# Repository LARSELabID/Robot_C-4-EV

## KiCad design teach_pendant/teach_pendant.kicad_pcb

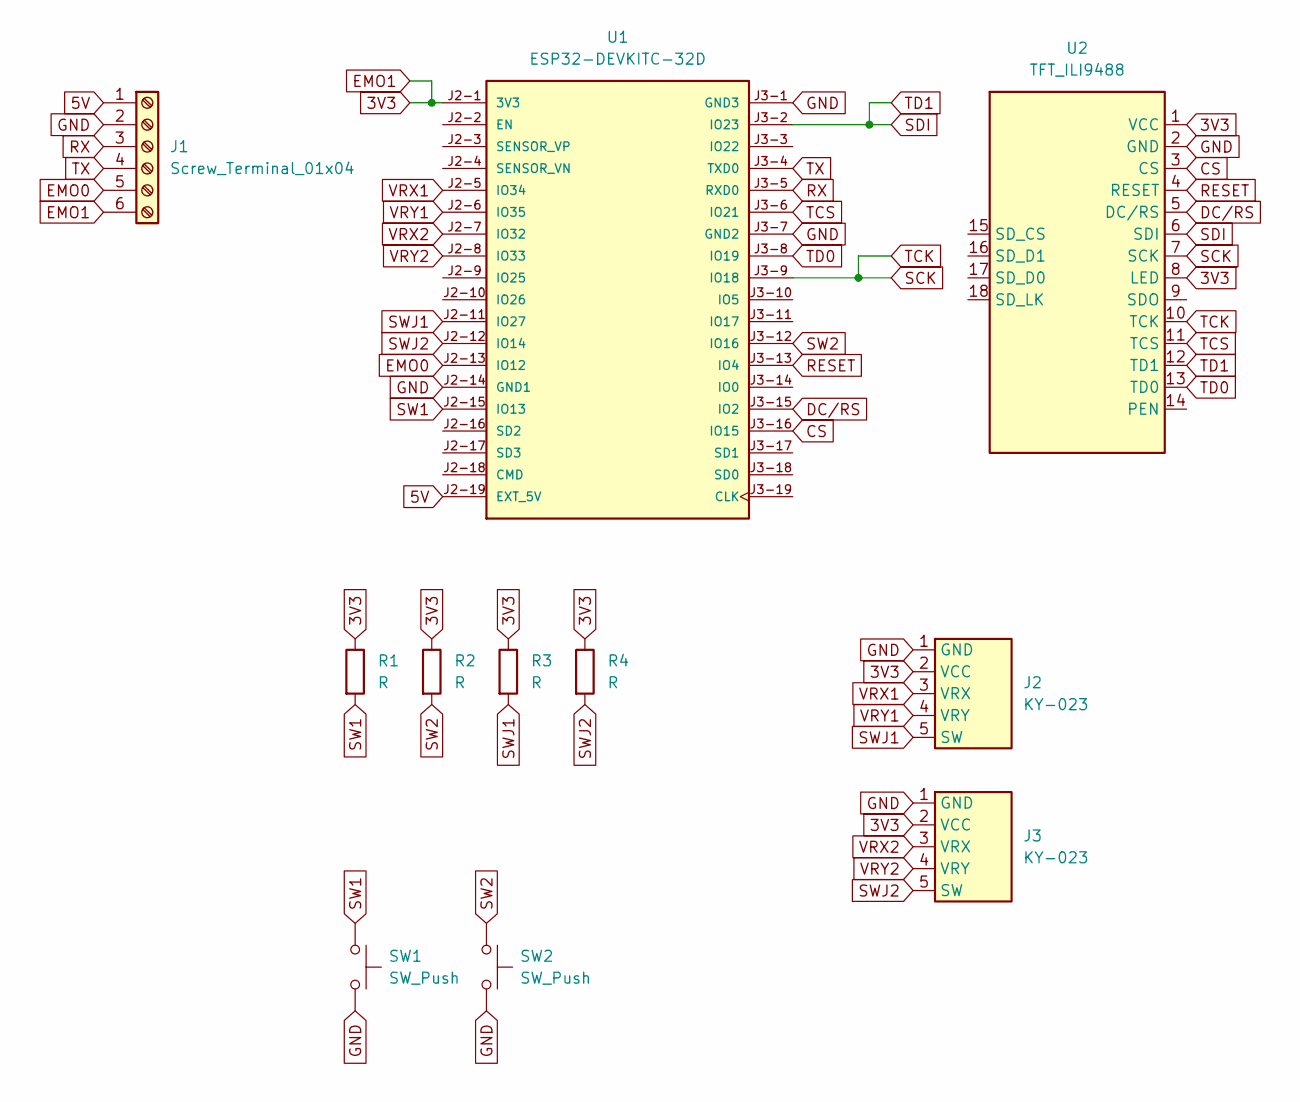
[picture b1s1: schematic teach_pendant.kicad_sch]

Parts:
J1: Screw_Terminal_01x04; TerminalBlock_Phoenix_MKDS-1,5-6-5.08_1x06_P5.08mm_Horizont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
J2, J3: KY-023; KY-023 Joystick-Module
R1, R2, R3, R4: R; R_Axial_DIN0207_L6.3mm_D2.5mm_P7.62mm_Horizontal
SW1, SW2: SW_Push; SW_FSM8JH_huella
U1: ESP32-DEVKITC-32D; MODULE_ESP32-DEVKITC-32D; PARTREV V4
U2: TFT_ILI9488

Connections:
3V3: J1.6, J2.2 (VCC), J3.2 (VCC), R1.1, R2.1, R3.1, R4.1, U1.J2-1 (3V3), U2.1 (VCC), U2.8 (LED)
5V: J1.1, U1.J2-19 (EXT_5V)
CS: U1.J3-16 (IO15), U2.3 (CS)
DC/RS: U1.J3-15 (IO2), U2.5 (DC/RS)
EMO0: J1.5, U1.J2-13 (IO12)
GND: J1.2, J2.1 (GND), J3.1 (GND), SW1.2, SW2.2, U1.J2-14 (GND1), U1.J3-1 (GND3), U1.J3-7 (GND2), U2.2 (GND)
RESET: U1.J3-13 (IO4), U2.4 (RESET)
RX: J1.3, U1.J3-5 (RXD0)
SCK: U1.J3-9 (IO18), U2.7 (SCK), U2.10 (TCK)
SDI: U1.J3-2 (IO23), U2.6 (SDI), U2.12 (TD1)
SW1: R1.2, SW1.1, U1.J2-15 (IO13)
SW2: R2.2, SW2.1, U1.J3-12 (IO16)
SWJ1: J2.5 (SW), R3.2, U1.J2-11 (IO27)
SWJ2: J3.5 (SW), R4.2, U1.J2-12 (IO14)
TCS: U1.J3-6 (IO21), U2.11 (TCS)
TD0: U1.J3-8 (IO19), U2.13 (TD0)
TX: J1.4, U1.J3-4 (TXD0)
VRX1: J2.3 (VRX), U1.J2-5 (IO34)
VRX2: J3.3 (VRX), U1.J2-7 (IO32)
VRY1: J2.4 (VRY), U1.J2-6 (IO35)
VRY2: J3.4 (VRY), U1.J2-8 (IO33)

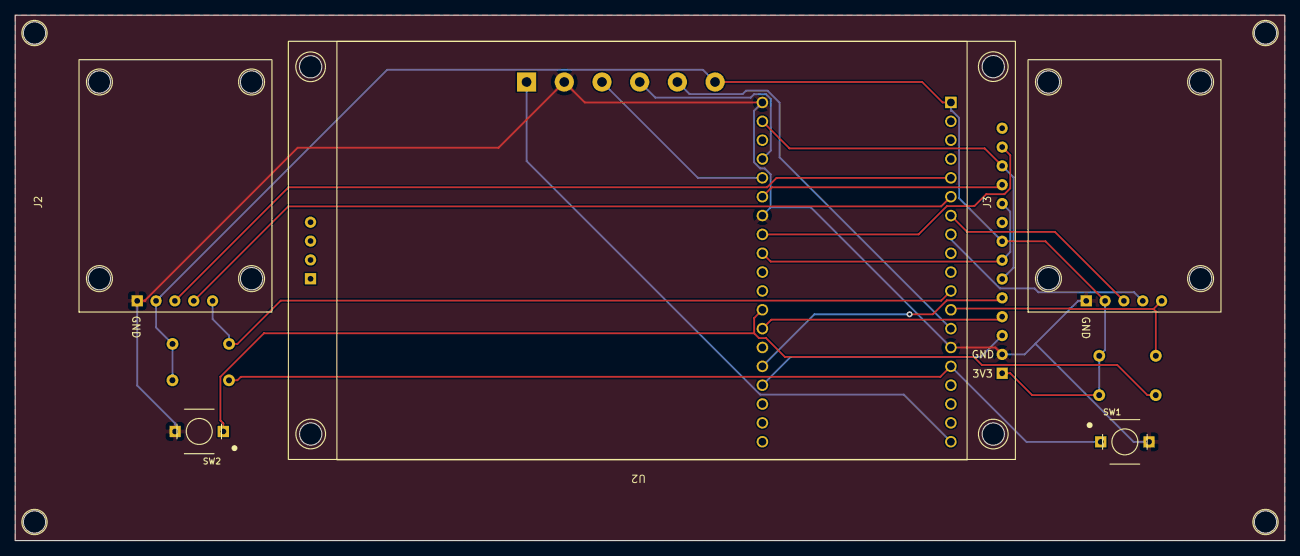
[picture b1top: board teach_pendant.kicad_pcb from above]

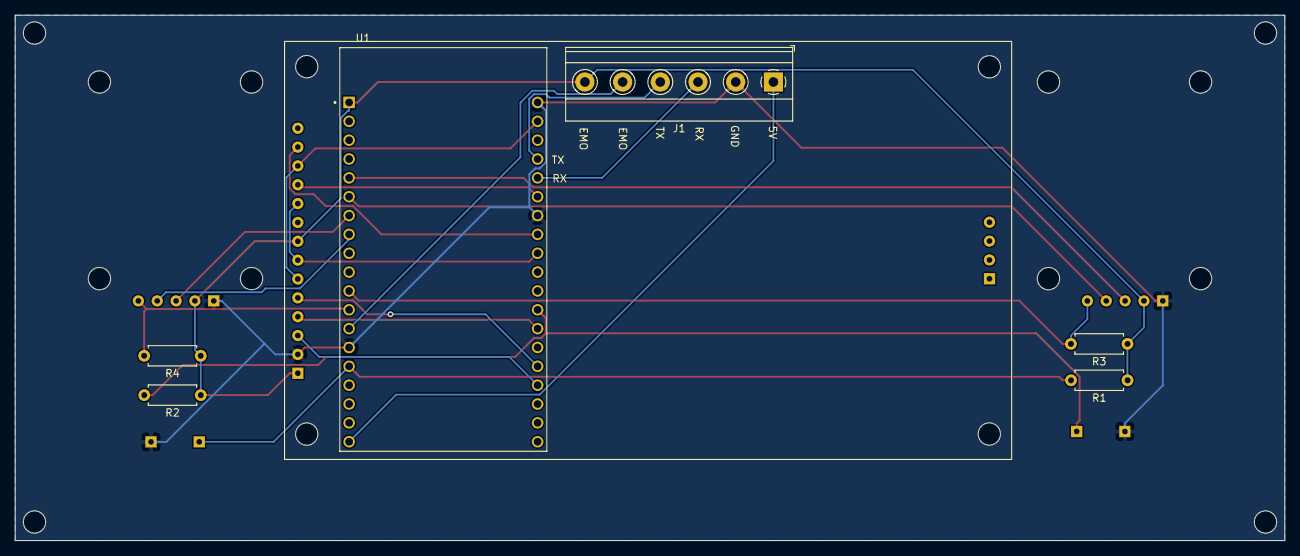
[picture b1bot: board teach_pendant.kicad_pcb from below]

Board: 2 copper layers, 171.1 x 70.8 mm, 11 parts (6 on the bottom side), 21 nets.

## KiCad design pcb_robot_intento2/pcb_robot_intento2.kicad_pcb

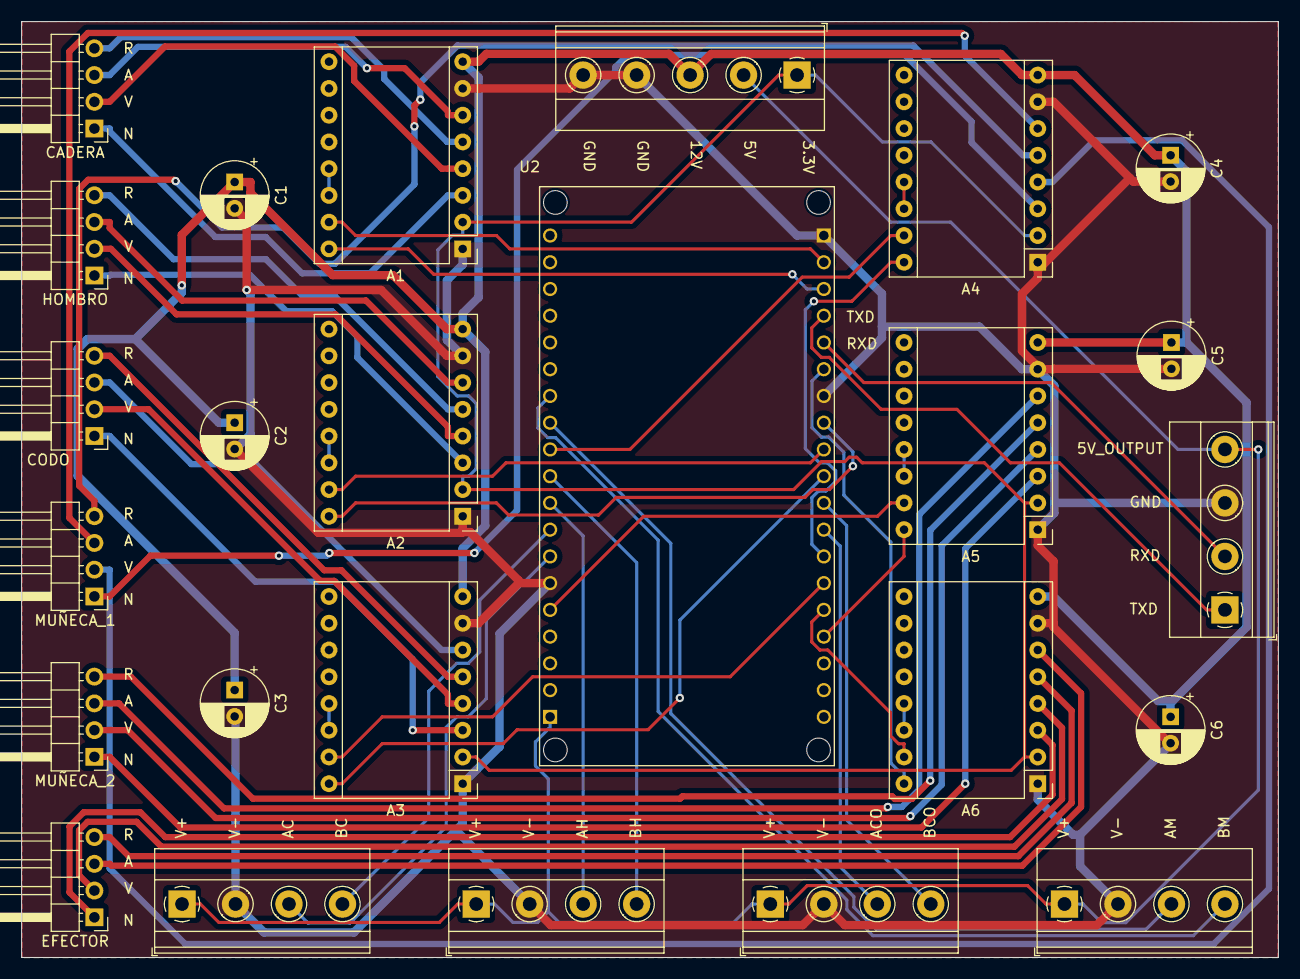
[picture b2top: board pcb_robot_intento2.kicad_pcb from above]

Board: 2 copper layers, 119.4 x 88.9 mm, 25 parts (0 on the bottom side), 56 nets.

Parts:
A1, A2, A3, A4, A5, A6: Pololu_Breakout_A4988; Pololu_Breakout-16_15.2x20.3mm
C1, C2, C3, C4, C5, C6: C_Polarized; CP_Radial_D6.3mm_P2.50mm
CADERA: Conn_01x04_Pin; PinHeader_1x04_P2.54mm_Horizontal
CODO: Conn_01x04_Pin; PinHeader_1x04_P2.54mm_Horizontal
EFECTOR: Conn_01x04_Pin; PinHeader_1x04_P2.54mm_Horizontal
HOMBRO: Conn_01x04_Pin; PinHeader_1x04_P2.54mm_Horizontal
J1: Screw_Terminal_01x05; TerminalBlock_Phoenix_MKDS-1,5-5-5.08_1x05_P5.08mm_Horizont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
J8, J9, J10, J11, J12: Screw_Terminal_01x04; TerminalBlock_Phoenix_MKDS-1,5-4-5.08_1x04_P5.08mm_Horizont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
MUÑECA_1, MUÑECA_2: Conn_01x04_Pin; PinHeader_1x04_P2.54mm_Horizontal
U2: ESP32_NODEMCU

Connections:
3V3: A1.2 (VDD), A2.2 (VDD), A3.2 (VDD), A4.2 (VDD), A5.2 (VDD), A6.2 (VDD), J1.1
5V: J1.2, J8.1, J9.1, J10.1, J11.1, J12.4, U2.J5_1 (5V)
12V: A1.8 (VMOT), A2.8 (VMOT), A3.8 (VMOT), A4.8 (VMOT), A5.8 (VMOT), A6.8 (VMOT), C1.1, C2.1, C3.1, C4.1, C5.1, C6.1, J1.3
AC: A1.6 (2B), CADERA.3
ACO: A3.6 (2B), CODO.3
AE: A6.6 (2B), EFECTOR.3
AH: A2.6 (2B), HOMBRO.3
AM1: A4.6 (2B), MUÑECA_1.3
AM2: A5.6 (2B), MUÑECA_2.3
DIR_C: A1.16 (DIR), U2.J4_3 (G22)
DIR_CO: A3.16 (DIR), U2.J4_10 (G5)
DIR_E: A6.16 (DIR), U2.J4_6 (G21)
DIR_H: A2.16 (DIR), U2.J4_8 (G19)
DIR_M1: A4.16 (DIR), U2.J4_13 (G4)
DIR_M2: A5.16 (DIR), U2.J4_16 (G15)
FAC: J8.3, U2.J5_7 (G12)
FACO: J10.3, U2.J4_12 (G16)
FAH: J9.3, U2.J5_9 (G27)
FAM: J11.3, U2.J5_12 (G33)
FBC: J8.4, U2.J5_8 (G14)
FBCO: J10.4, U2.J4_11 (G17)
FBH: J9.4, U2.J5_10 (G26)
FBM: J11.4, U2.J5_13 (G32)
GND: A1.1 (GND), A1.7 (GND), A2.1 (GND), A2.7 (GND), A3.1 (GND), A3.7 (GND), A4.1 (GND), A4.7 (GND), A5.1 (GND), A5.7 (GND), A6.1 (GND), A6.7 (GND), C1.2, C2.2, C3.2, C4.2, C5.2, C6.2, J1.4, J1.5, J8.2, J9.2, J10.2, J11.2, J12.3, U2.J4_1 (GND_J4_1), U2.J4_7 (GND_J4_7), U2.J5_6 (GND_J5_6)
NC: A1.3 (1B), CADERA.1
NCO: A3.3 (1B), CODO.1
NE: A6.3 (1B), EFECTOR.1
NH: A2.3 (1B), HOMBRO.1
NM1: A4.3 (1B), MUÑECA_1.1
NM2: A5.3 (1B), MUÑECA_2.1
unnamed: A1.13 (~RESET), A1.14 (~SLEEP)
unnamed: A2.13 (~RESET), A2.14 (~SLEEP)
unnamed: A3.13 (~RESET), A3.14 (~SLEEP)
unnamed: A4.13 (~RESET), A4.14 (~SLEEP)
unnamed: A5.13 (~RESET), A5.14 (~SLEEP)
unnamed: A6.13 (~RESET), A6.14 (~SLEEP)
RC: A1.5 (2A), CADERA.4
RCO: A3.5 (2A), CODO.4
RE: A6.5 (2A), EFECTOR.4
RH: A2.5 (2A), HOMBRO.4
RM1: A4.5 (2A), MUÑECA_1.4
RM2: A5.5 (2A), MUÑECA_2.4
RX: J12.2, U2.J4_5 (RXD)
STEP_C: A1.15 (STEP), U2.J4_2 (G23)
STEP_CO: A3.15 (STEP), U2.J4_14 (G0)
STEP_E: A6.15 (STEP), U2.J4_15 (G2)
STEP_H: A2.15 (STEP), U2.J4_9 (G18)
STEP_M1: A4.15 (STEP), U2.J5_11 (G25)
STEP_M2: A5.15 (STEP), U2.J5_5 (G13)
TX: J12.1, U2.J4_4 (TXD)
VC: A1.4 (1A), CADERA.2
VCO: A3.4 (1A), CODO.2
VE: A6.4 (1A), EFECTOR.2
VH: A2.4 (1A), HOMBRO.2
VM1: A4.4 (1A), MUÑECA_1.2
VM2: A5.4 (1A), MUÑECA_2.2

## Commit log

2024-11-16 Piezas mecánicas del robot
    Piezas mecánicas
